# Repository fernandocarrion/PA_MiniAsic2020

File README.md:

# PA_MiniAsic2020
Track Power Amplifier views from the Mini Asic 2020 shuttle

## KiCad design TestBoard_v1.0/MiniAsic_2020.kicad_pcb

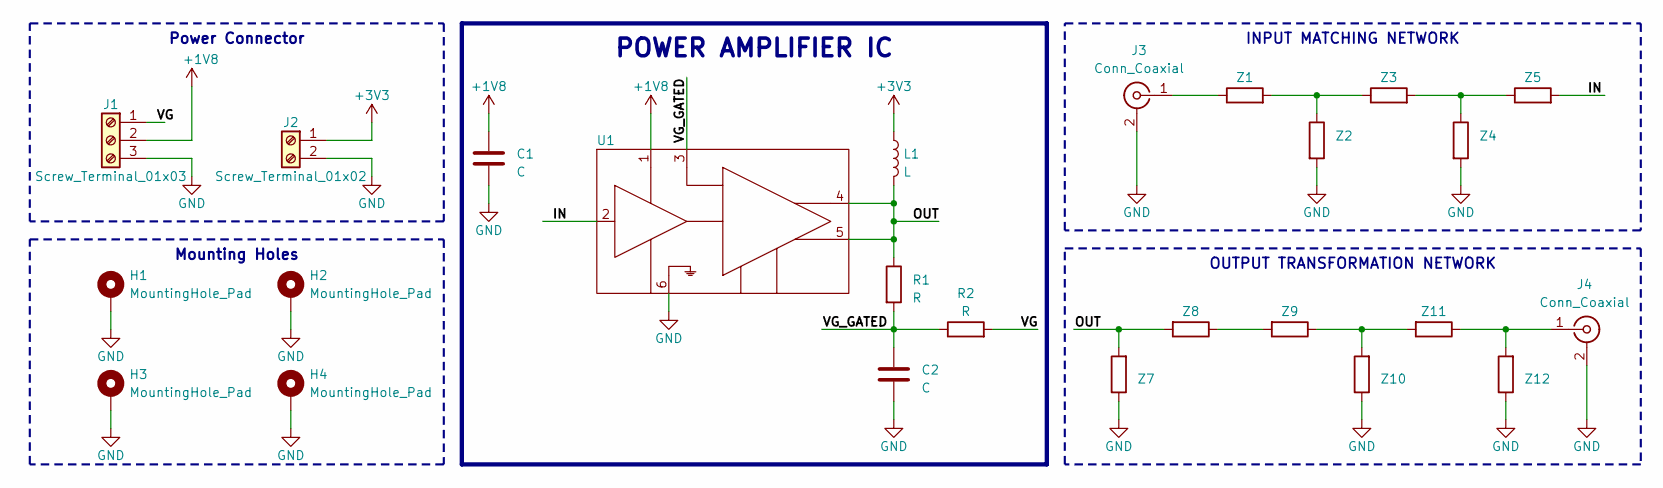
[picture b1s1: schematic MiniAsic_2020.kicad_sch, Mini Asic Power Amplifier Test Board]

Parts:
C1, C2: C; C_0603_1608Metric
H1, H2, H3, H4: MountingHole_Pad; MountingHole_3.2mm_M3_Pad_Via
J1: Screw_Terminal_01x03; TerminalBlock_bornier-3_P5.08mm
J2: Screw_Terminal_01x02; TerminalBlock_bornier-2_P5.08mm
J3, J4: Conn_Coaxial; SMA_Amphenol_901-143_Horizontal
L1: L; L_0603_1608Metric
R1, R2: R; R_0603_1608Metric
U1: MiniAsic2020_MPW_Chip
Z1, Z2, Z3, Z4, Z5, Z7, Z8, Z9, Z10, Z11, Z12: Z; R_0603_1608Metric

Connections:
+1V8: C1.1, J1.2, U1.1 (DRV_VDD)
+3V3: J2.1, L1.1
/IN: U1.2 (IN), Z5.2
/OUT: L1.2, R1.1, U1.4 (OUT_1), U1.5 (OUT_2), Z7.2, Z8.2
/VG: J1.1, R2.2
/VG_GATED: C2.1, R1.2, R2.1, U1.3 (VG)
GND: C1.2, C2.2, H1.1, H2.1, H3.1, H4.1, J1.3, J2.2, J3.2 (Ext), J4.2 (Ext), U1.6 (GND), Z2.2, Z4.2, Z7.1, Z10.1, Z12.1
unnamed: J3.1 (In), Z1.1
unnamed: J4.1 (In), Z11.1, Z12.2
unnamed: Z1.2, Z2.1, Z3.1
unnamed: Z3.2, Z4.1, Z5.1
unnamed: Z8.1, Z9.2
unnamed: Z9.1, Z10.2, Z11.2

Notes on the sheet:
INPUT MATCHING NETWORK
Mounting Holes
OUTPUT TRANSFORMATION NETWORK
Power Connector
POWER AMPLIFIER IC

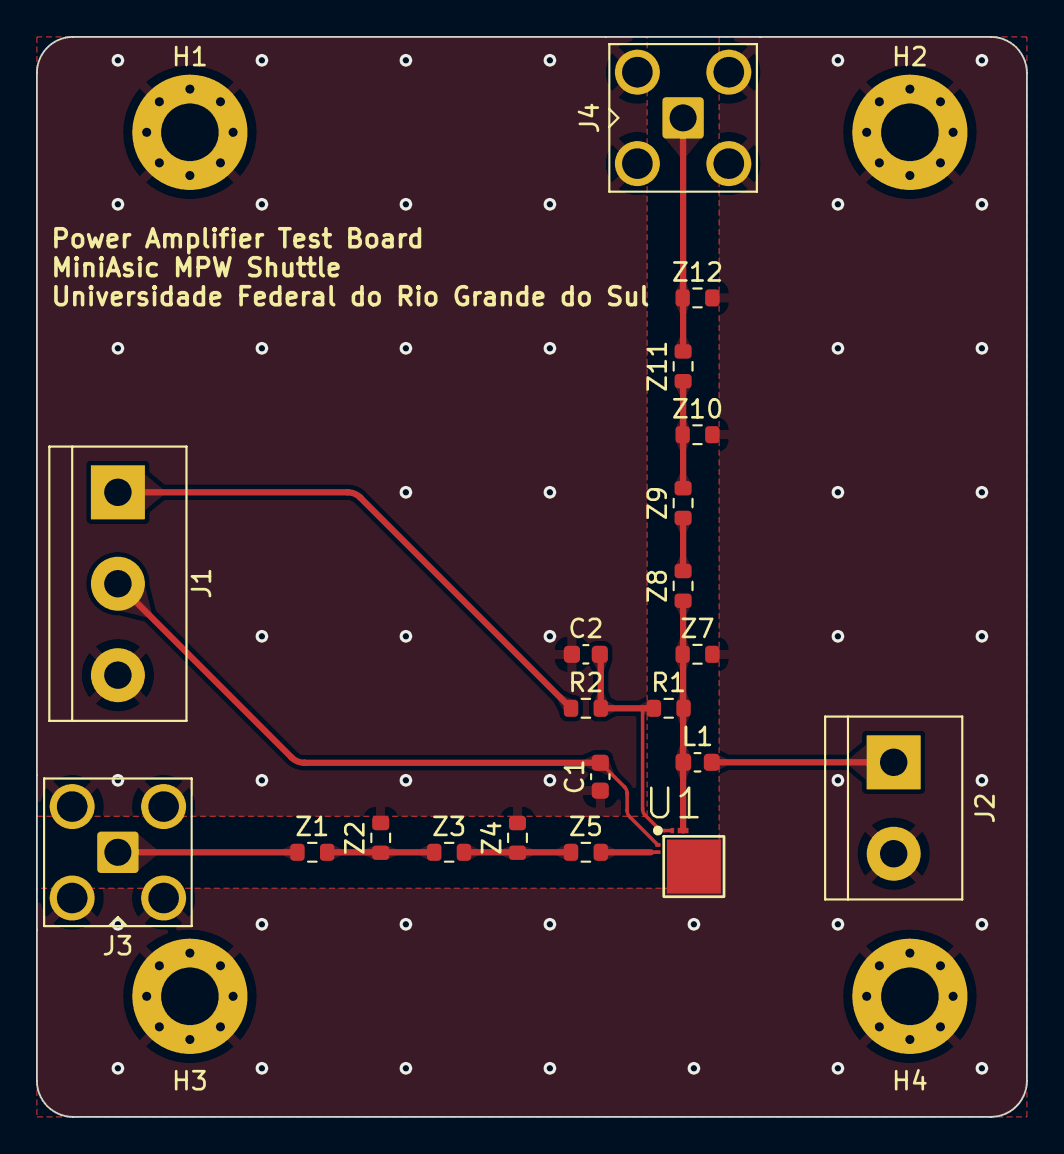
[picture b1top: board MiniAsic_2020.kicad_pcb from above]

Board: 2 copper layers, 55.0 x 60.0 mm, 25 parts (0 on the bottom side), 13 nets.

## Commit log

2023-07-16 Create MiniAsic_2020.kicad_pro
    Add Kicaid PCB project for V1.0 of the Test Board.
2023-07-16 Add files via upload
    Add Kicad PCB project files.
2023-07-16 add Library Footprint
2023-07-16 Schematic update and initial placement
2023-07-18 Initial routing
2023-07-19 New placement focused on the transmission lines
2023-07-21 add gnd planes and via array
2023-07-22 Connect IC gnd pad, clean drc, add dimensions, generate gerbers, and export schematic/3d views
2023-07-22 Add 3D view to README.md
